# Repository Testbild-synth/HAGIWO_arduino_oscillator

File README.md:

# HAGIWO 019/022/023 Triple Oscillator (FM/CHORD/ADDITIVE)

4HP through hole version of the HAGIWO FM/additive/chord oscillator with mode switch and gain input.

This module is basically my PCB version of the HAGIWO osc, heavily inspired by [luis lutz version](https://github.com/luislutz/Arduino-VDCO).
The main difference is since I could not get his code to work without major audio problems, I rewrote the entire thing myself.

The module combines three different oscillators from HAGIWO,  with a mode switch (and mode cv input) to switch between them.
Additionally, it has a gain input that normals so that it is only used when you plug in a jack.

### STATUS: Revision 1.1 PCB with slight modifications to make the build easier.

## Hardware and PCB

You can find the schematic and BOM in the root folder.
For the potentiometers, any value between 10k and 100k should be fine.

The module has three PCBs: a panel PCB, a main PCB and a controls pcb.
You can order them on any common PCB manufacturing service, I used JLCPCB. For the circuit PCBs, standard settings should be fine.
For the panel, since it has copper exposed, make sure to choose a lead free surface finish (LeadFree HASL, ENIG) and/or spraypaint your panels so that you don't get lead on your hands.

Assembly is pretty straight forward. Since it is so crowded, make sure to do the resistors first before the headers so you have more space to work.

Also make sure to put the headers connecting both PCBs in the correct direction so that the arduino faces to the back.

The only thing there is to tune is a trimpot that sets output gain (as arduino is 0-5V output and I wanted to be able to make mine louder). Tune it to your liking.

## Build

Most of the build is relatively straight forward. be sure to actually have fitting values for the resistors that need to be precise. These are indicated with % on the board and in the bom.      
One thing to watch out for is that due to size constraints I oriented one row of thonkiconn jacks to face another one and have the grounds go into the same hole.
So top two rows face each other, ground legs go into the same hole.

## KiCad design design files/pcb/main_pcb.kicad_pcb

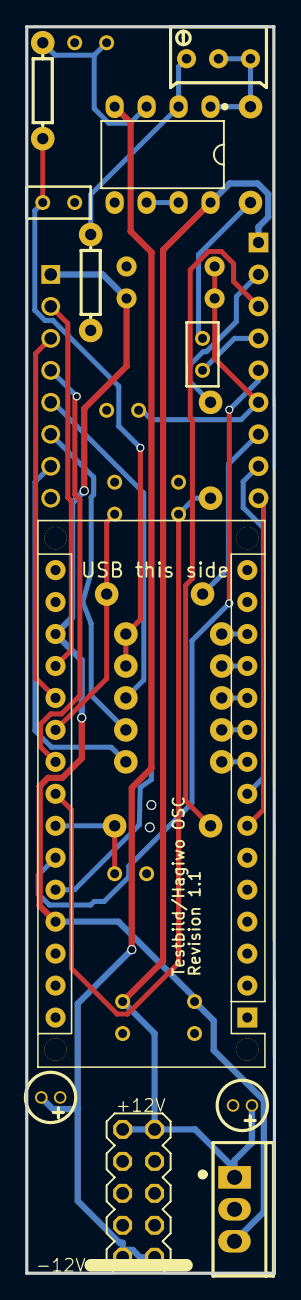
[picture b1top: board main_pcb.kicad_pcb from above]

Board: 2 copper layers, 19.7 x 99.1 mm, 30 parts (0 on the bottom side), 32 nets.

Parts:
C1, C2, C3, C4: 4.7n; RAD-0.1
C5: 10n; RAD-0.1
C6: 4.7u; RAD-0.1
C7, C8: 10u; CAP-D4.0×F1.5
C9, C10, C11: 100n; RAD-0.1
D1, D2: BAT43; DO-34_BD1.6-L3.0-P7.00-D0.6-RD
GAIN: 100k; TRIMPOT
H1: Header-Male-2.54_1x8; HDR-TH_8P-P2.54-V-M
J1: HDR-M-2.54_1x9; HDR-M-2.54_1X9
R1, R2, R7: 22k; R_AXIAL-0.3
R3: 499k 0.5%; R_AXIAL-0.3
R4, R9: 3.9k 0.5%; R_AXIAL-0.3
R5, R6, R8: 4k7; R_AXIAL-0.3
R10: 220; R_AXIAL-0.3
R11: 47k; R_AXIAL-0.3
U1: ARDUINO_NANO; ARDUINO_NANO_WITHMOUNTINGHOLES
U2: TL072CP; DIP-8_L9.4-W6.4-P2.54-LS9.1-BL
U3: 7805; TO-220-3_L10.0-W4.5-P2.54-L

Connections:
+5V: C9.2, D1.1, H1.1, U1.18, U1.27, U3.3
+12V: C8.1, C10.1, J1.1, U2.8, U3.1
-12V: C7.2, U2.4
C4_1: C4.1, R3.2, R4.2, R9.1
FRQPOT: H1.2, U1.19
GND: C1.1, C2.1, C3.1, C4.2, C5.2, C7.1, C8.2, C9.1, C10.2, C11.1, D2.2, H1.8, R11.1, U1.4, U1.29, U2.5, U3.2
GVC: J1.5, U1.25
LED1: H1.5, R5.2
LED2: H1.6, R6.2
LED3: H1.7, R8.2
MODECV: J1.7, R7.2
OUT: C6.2, J1.4
P1CV: J1.2, R2.2
P1POT: H1.3, U1.20
P2CV: J1.3, R1.2
P2POT: H1.4, U1.22
R9_2: C5.1, R9.2, U2.3
R10_1: C6.1, R10.1
SW1: J1.8, U1.8
SW2: J1.9, U1.7
U1_9: R8.1, U1.9
U1_10: R6.1, U1.10
U1_11: R5.1, U1.11
U1_12: R4.1, U1.12
U1_13: R3.1, U1.13
U1_21: C3.2, R7.1, U1.21
U1_23: C2.2, R2.1, U1.23
U1_24: C1.2, R1.1, U1.24
U2_1: GAIN.2, GAIN.3, R10.2, U2.1
U2_2: GAIN.1, R11.2, U2.2
U2_6: U2.6, U2.7
V_OCT: C11.2, D1.2, D2.1, J1.6, U1.26

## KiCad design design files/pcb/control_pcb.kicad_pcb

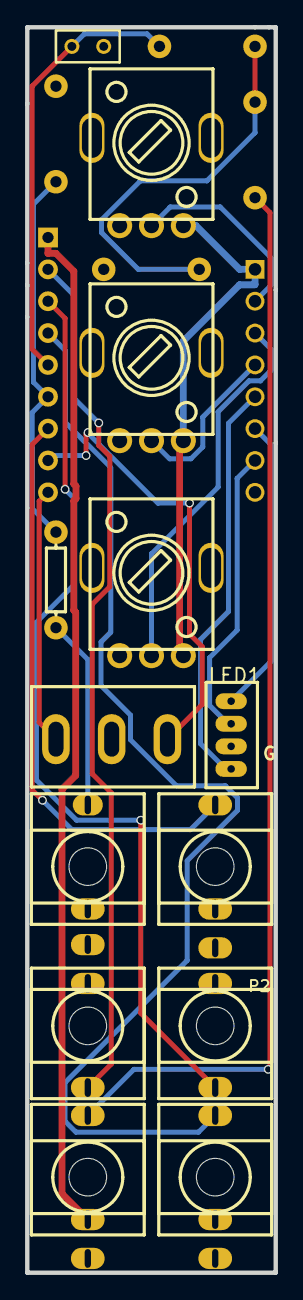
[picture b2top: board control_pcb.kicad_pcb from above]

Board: 2 copper layers, 19.8 x 99.3 mm, 17 parts (0 on the bottom side), 18 nets.

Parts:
C12: 100n; RAD-0.1
FRQ: 10-100k; R09-5KΩ
H2: Header-Male-2.54_1x8; HDR-TH_8P-P2.54-V-M
J1: HDR-M-2.54_1x9; HDR-M-2.54_1X9
J2: P1_CV; THONKICONN_1
J3: MODE_CV; THONKICONN_1
J7: GAIN_CV; THONKICONN_1
J8: OUT; THONKICONN_1
LED1: LED RGB; GEK_RGB_LED
P1_POT, P2_POT: 10-100k; R09-5KΩ
R12: 100; R_AXIAL-0.3
R13: 330k; R_AXIAL-0.3
R14: 47k; R_AXIAL-0.3
R15: 1k; R_AXIAL-0.3
R16: 68k; R_AXIAL-0.3
U4: TOGGLE SWITCH SPDT; MINI TOGGLE SWITCH SPDT ON-ON

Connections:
+5V: FRQ.3, H2.1, P1_POT.3, P2_POT.3
+12V: J1.1, J7.2
FRQPOT: FRQ.2, H2.2
GND: C12.1, FRQ.1, H2.8, J2.1, J2.2, J3.1, J3.2, J7.1, J8.1, LED1.2, P1_POT.1, P2_POT.1, R13.2, R16.2, U4.1
GVC: C12.2, J1.5, R15.1
J7_3: J7.3, R14.2
LED1: H2.5, LED1.1
LED2: H2.6, LED1.4
LED3: H2.7, LED1.3
MODECV: J1.7, J3.3
OUT: J1.4, J8.3
P1CV: J1.2, J2.3
P1POT: H2.3, P2_POT.2
P2POT: H2.4, P1_POT.2
R14_1: R14.1, R15.2, R16.1
SW1: J1.8, U4.2
SW2: J1.9, U4.3
V_OCT: J1.6, R12.1, R13.1

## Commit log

2022-03-14 file upload
2022-03-14 images
2022-03-14 upload BOM
2022-03-14 image upload
2022-03-14 panel_design update
2023-01-16 new files for fixed power lane and better spaced components
2025-02-14 revision 1.1 pcb
    mainly better footprints, slightly more space for the power adapter
2025-02-14 new images for 1.1 pcbs
2025-02-14 new panel for 1.1 revision
2026-04-17 [Add] the 5 function mod code from modulove with rewritten gen seq
